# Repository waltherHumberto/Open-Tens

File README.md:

# Open-Tens
The goal of this project is to develop an open-source Transcutaneous Electrical Nerve Stimulation (TENS) system. TENS is a therapeutic technique that involves the application of low-voltage electrical currents to the skin, primarily for pain relief. This project aims to provide a platform for individuals and healthcare professionals to build and customize their own TENS devices using readily available hardware components.

The open-source nature of this project encourages collaboration, innovation, and the sharing of knowledge among developers and users. By making the TENS system accessible to a wider audience, we hope to empower individuals to explore alternative pain management techniques and contribute to the advancement of TENS technology.

Key Features and Objectives:

    Hardware Design: The project will provide detailed documentation and schematics for designing and building a TENS device. The emphasis will be on using affordable and easily obtainable components, making it accessible to hobbyists, researchers, and healthcare professionals.

    Software Development: The project will include software libraries and interfaces to control the TENS device. The software will allow users to adjust parameters such as frequency, pulse width, and intensity, providing a customizable and user-friendly experience.

    Safety and Effectiveness: Ensuring the safety and efficacy of the TENS system is of utmost importance. The project will focus on providing guidelines, best practices, and recommendations for safe usage, including electrical safety precautions and appropriate electrode placement.

    Community and Collaboration: The project aims to foster a supportive and collaborative community of developers, researchers, and users. This will be achieved through an online forum, issue tracking system, and regular updates to encourage discussions, bug reporting, feature requests, and contributions from the community.

By creating an open-source TENS system, we hope to democratize access to this pain management technique, encourage further research and development, and improve the lives of individuals suffering from chronic pain. Join us in this journey of innovation, empowerment, and open science.

Note: This project is not intended to replace professional medical advice or treatment. Users should consult with healthcare professionals before using the TENS system for any medical conditions or concerns.

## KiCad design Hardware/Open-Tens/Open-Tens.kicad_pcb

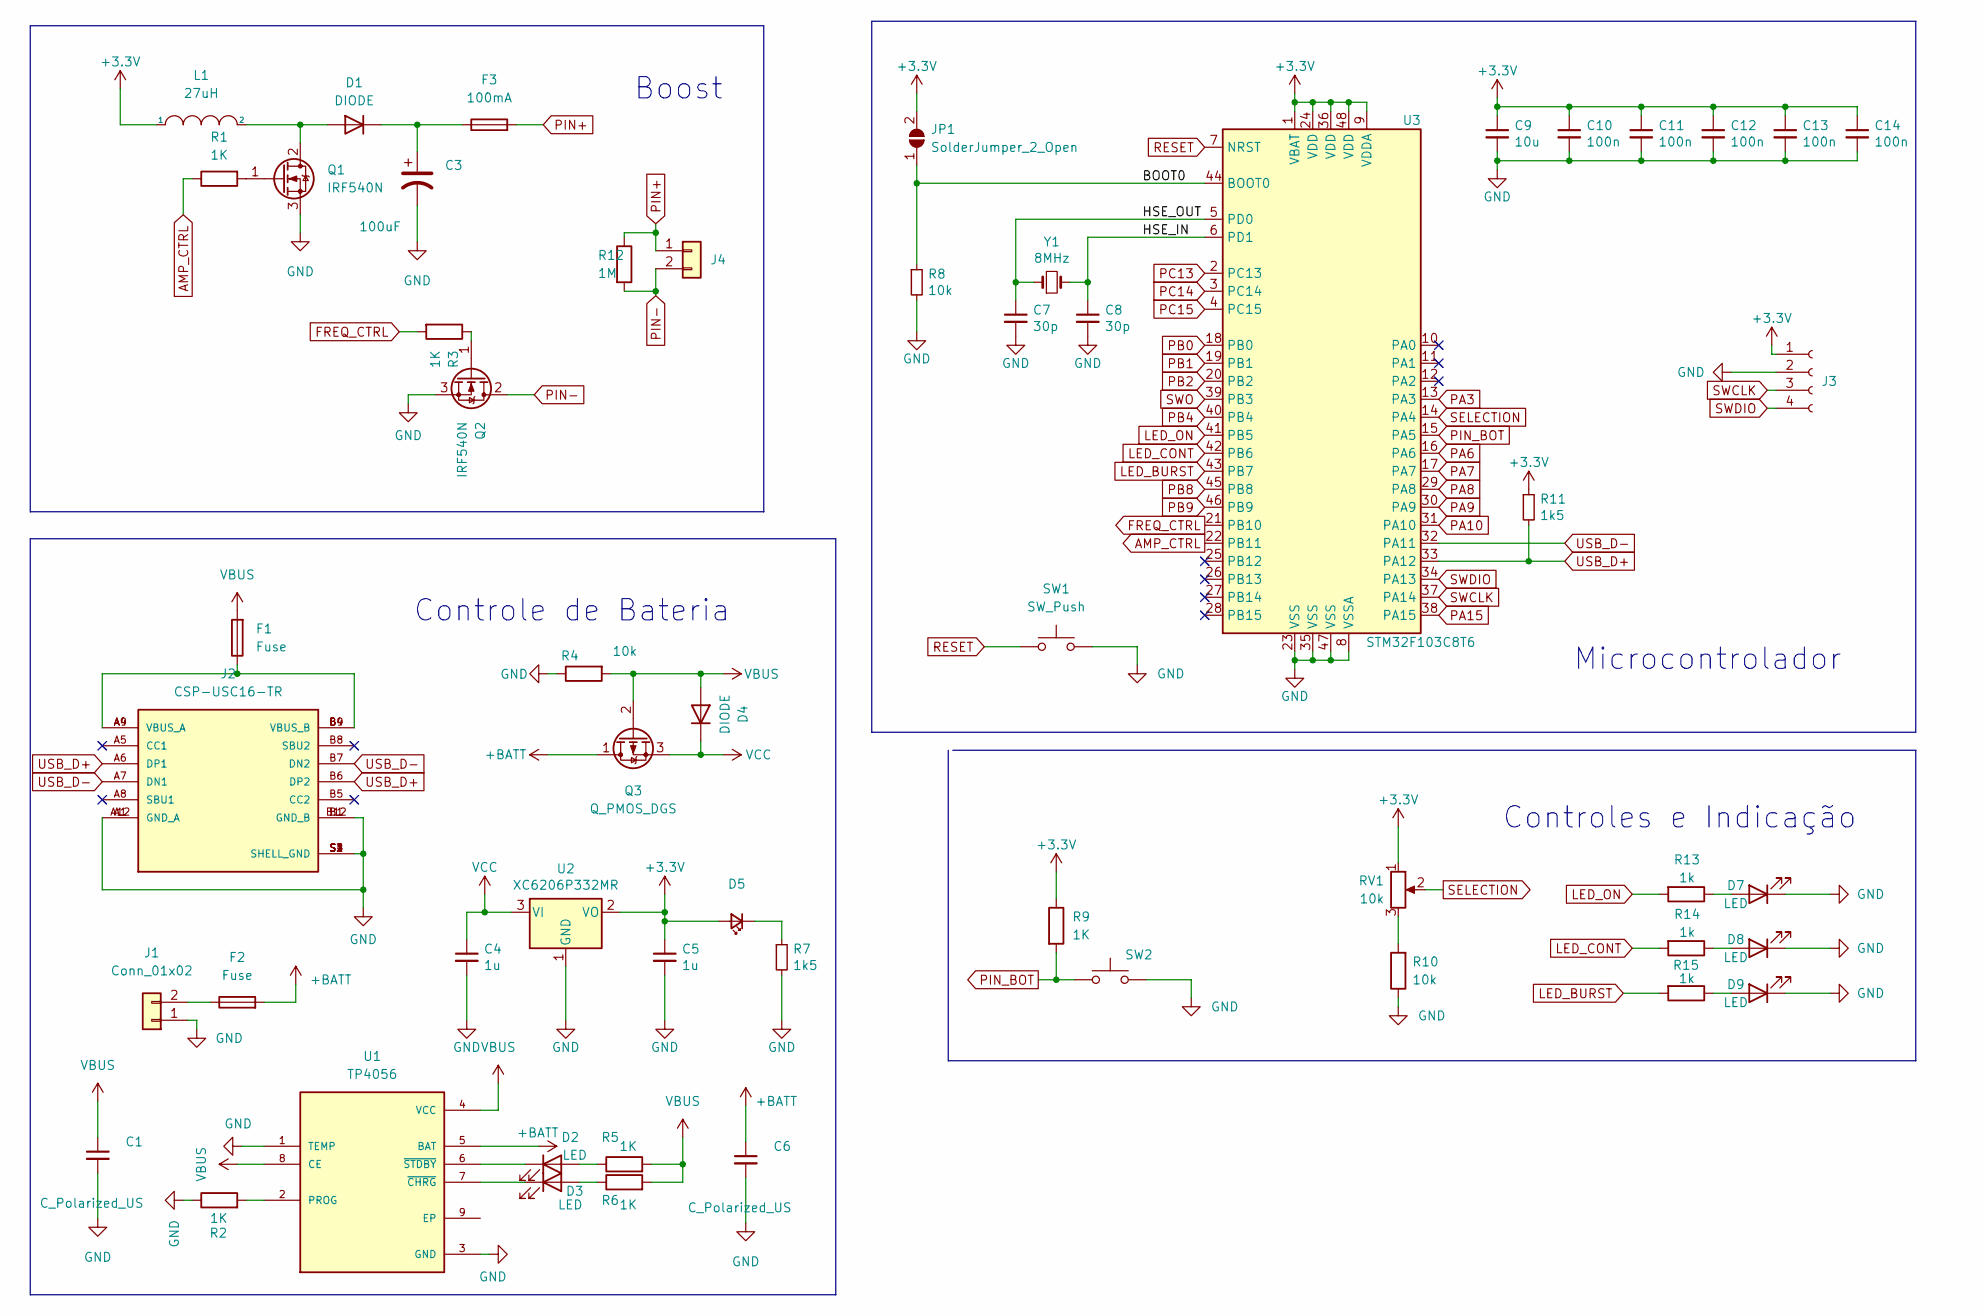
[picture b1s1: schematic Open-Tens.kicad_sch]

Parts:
C1, C6: C_Polarized_US; C_1210_3225Metric
C3: 100uF; CP_Radial_D10.0mm_P7.50mm
C4, C5: 1u; C_0603_1608Metric; LCSC Part # C15849
C7, C8: 30p; C_0402_1005Metric; LCSC Part # C1570
C9: 10u; C_1210_3225Metric; LCSC Part # C19666
C10, C11, C12, C13, C14: 100n; C_0402_1005Metric; LCSC Part # C1525
D1, D4: DIODE; D_1210_3225Metric
D2, D3, D7, D8, D9: LED; LED_D5.0mm_FlatTop
D5: LED; LED_D5.0mm_FlatTop; LCSC Part # C72043
F1, F2: Fuse; R_1206_3216Metric
F3: 100mA; R_1206_3216Metric
J1: Conn_01x02; PinSocket_1x02_P2.54mm_Vertical
J2: CSP-USC16-TR; USB_C_Receptacle_Palconn_UTC16-G; PARTREV A0
J3: Conn_01x04_Female; PinSocket_1x04_P2.54mm_Vertical
J4: Conn_01x02; R_Axial_DIN0309_L9.0mm_D3.2mm_P12.70mm_Horizontal
JP1: SolderJumper_2_Open; PinSocket_1x02_P2.54mm_Vertical
L1: 27uH; L_Taiyo-Yuden_NR-80xx_HandSoldering
Q1, Q2: IRF540N; TO-220-3_Vertical
Q3: Q_PMOS_DGS; SOT-23-3
R1, R2, R3, R5, R6, R9: 1K; R_0603_1608Metric
R4, R10: 10k; R_0603_1608Metric
R7: 1k5; R_0603_1608Metric; LCSC Part # C22843
R8: 10k; R_0603_1608Metric; LCSC Part # C25744
R11: 1k5; R_0603_1608Metric; LCSC Part # C25867
R12: 1M; R_Axial_DIN0309_L9.0mm_D3.2mm_P12.70mm_Horizontal
R13, R14, R15: 1k; R_0603_1608Metric
RV1: 10k; Potentiometer_Bourns_3296W_Vertical
SW1, SW2: SW_Push; SW_Push_1P1T_NO_CK_KSC6xxJ
U1: TP4056; SOP-8_3.9x4.9mm_P1.27mm
U2: XC6206P332MR; SOT-23; LCSC Part # C5446
U3: STM32F103C8T6; LQFP-48_7x7mm_P0.5mm; LCSC Part # C8734
Y1: 8MHz; Crystal_SMD_5032-2Pin_5.0x3.2mm; LCSC Part # C115962

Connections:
+3.3V: C5.1, C9.1, C10.1, C11.1, C12.1, C13.1, C14.1, D5.2 (A), J3.1, JP1.2 (B), L1.1, R9.1, R11.1, RV1.1, U2.2 (VO), U3.1 (VBAT), U3.9 (VDDA), U3.24 (VDD), U3.36 (VDD), U3.48 (VDD)
+BATT: C6.1, F2.2, Q3.1 (D), U1.5 (BAT)
/BOOT0: JP1.1 (A), R8.1, U3.44 (BOOT0)
/HSE_IN: C8.1, U3.6 (PD1), Y1.2
/HSE_OUT: C7.1, U3.5 (PD0), Y1.1
AMP_CTRL: R1.1, U3.22 (PB11)
FREQ_CTRL: R3.2, U3.21 (PB10)
GND: C1.2, C3.2, C4.2, C5.2, C6.2, C7.2, C8.2, C9.2, C10.2, C11.2, C12.2, C13.2, C14.2, D7.1 (K), D8.1 (K), D9.1 (K), J1.1, J2.A1 (GND_A), J2.A12 (GND_A), J2.B1 (GND_B), J2.B12 (GND_B), J2.S1 (SHELL_GND), J2.S2 (SHELL_GND), J2.S3 (SHELL_GND), J2.S4 (SHELL_GND), J3.2, Q1.3 (S), Q2.3 (S), R2.1, R4.1, R7.2, R8.2, R10.1, SW1.2, SW2.2, U1.1 (TEMP), U1.3 (GND), U2.1 (GND), U3.8 (VSSA), U3.23 (VSS), U3.35 (VSS), U3.47 (VSS); also elsewhere on the board
LED_BURST: R15.2, U3.43 (PB7)
LED_CONT: R14.2, U3.42 (PB6)
LED_ON: R13.2, U3.41 (PB5)
unnamed: C3.1, D1.2 (K), F3.1
unnamed: D1.1 (A), L1.2, Q1.2 (D)
unnamed: D2.1 (K), U1.6 (~STDBY)
unnamed: D2.2 (A), R5.1
unnamed: D3.1 (K), U1.7 (~CHRG)
unnamed: D3.2 (A), R6.1
unnamed: D5.1 (K), R7.1
unnamed: D7.2 (A), R13.1
unnamed: D8.2 (A), R14.1
unnamed: D9.2 (A), R15.1
unnamed: F1.1, J2.A4 (VBUS_A), J2.A9 (VBUS_A), J2.B4 (VBUS_B), J2.B9 (VBUS_B)
unnamed: F2.1, J1.2
unnamed: Q1.1 (G), R1.2
unnamed: Q2.1 (G), R3.1
unnamed: R2.2, U1.2 (PROG)
unnamed: R10.2, RV1.3
PA3: U3.13 (PA3)
PA6: U3.16 (PA6)
PA7: U3.17 (PA7)
PA8: U3.29 (PA8)
PA9: U3.30 (PA9)
PA10: U3.31 (PA10)
PA15: U3.38 (PA15)
PB0: U3.18 (PB0)
PB1: U3.19 (PB1)
PB2: U3.20 (PB2)
PB4: U3.40 (PB4)
PB8: U3.45 (PB8)
PB9: U3.46 (PB9)
PC13: U3.2 (PC13)
PC14: U3.3 (PC14)
PC15: U3.4 (PC15)
PIN+: F3.2, J4.1, R12.1
PIN-: J4.2, Q2.2 (D), R12.2
PIN_BOT: R9.2, SW2.1, U3.15 (PA5); also elsewhere on the board
RESET: SW1.1, U3.7 (NRST); also elsewhere on the board
SELECTION: RV1.2, U3.14 (PA4)
SWCLK: J3.3, U3.37 (PA14)
SWDIO: J3.4, U3.34 (PA13)
SWO: U3.39 (PB3)
USB_D+: J2.A6 (DP1), J2.B6 (DP2), R11.2, U3.33 (PA12)
USB_D-: J2.A7 (DN1), J2.B7 (DN2), U3.32 (PA11)
VBUS: C1.1, D4.1 (A), F1.2, Q3.2 (G), R4.2, R5.2, R6.2, U1.4 (VCC), U1.8 (CE)
VCC: C4.1, D4.2 (K), Q3.3 (S), U2.3 (VI)

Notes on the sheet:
Controle de Bateria
Controles e Indicação
Boost
Microcontrolador

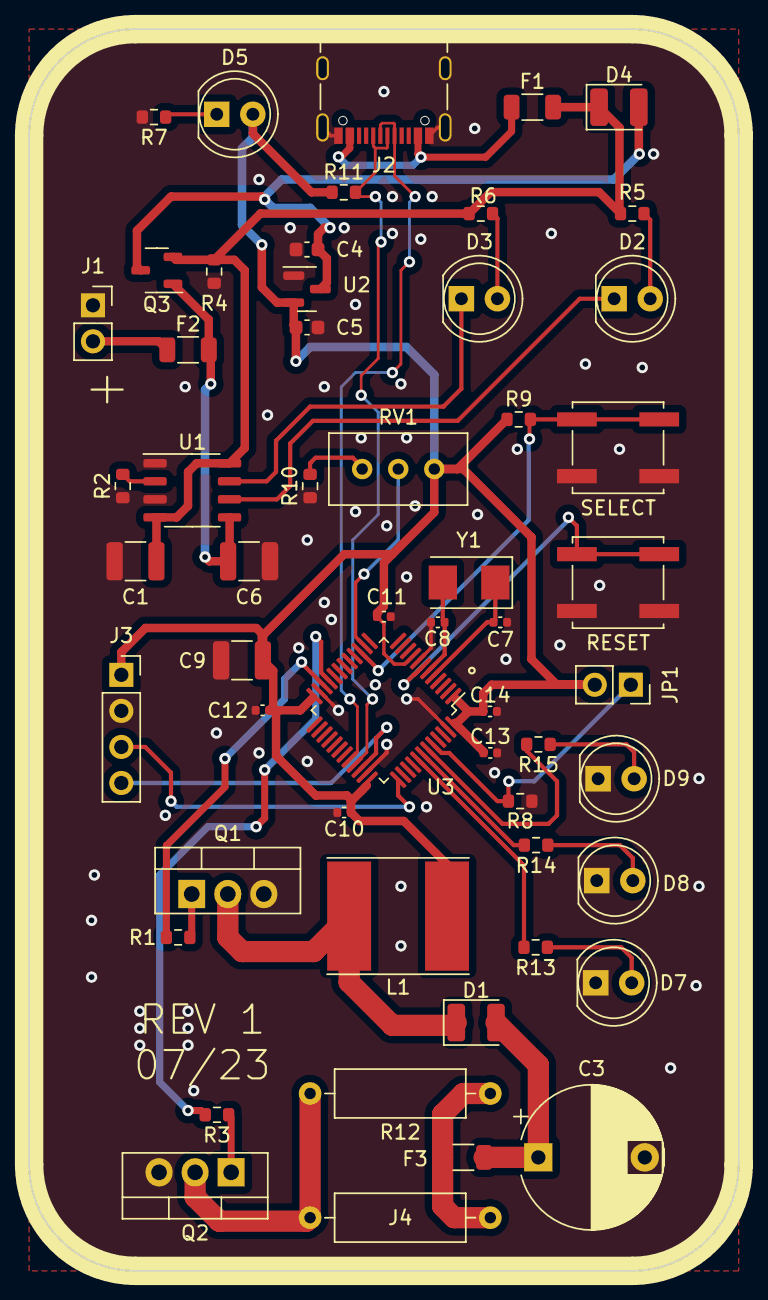
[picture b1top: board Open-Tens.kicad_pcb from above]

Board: 2 copper layers, 50.0 x 87.5 mm, 55 parts (0 on the bottom side), 38 nets.

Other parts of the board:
RESET: SW_Push; SW_Push_1P1T_NO_CK_KSC6xxJ
SELECT: SW_Push; SW_Push_1P1T_NO_CK_KSC6xxJ

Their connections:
GND: RESET.2, SELECT.2; also elsewhere on the board
PIN_BOT: SELECT.1; also elsewhere on the board
RESET: RESET.1; also elsewhere on the board

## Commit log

2023-07-06 Update README.md
    Adding context to README
2023-07-09 Saving to push
2023-07-11 Separando o esquematico falta colocar valores
2023-07-13 Trocando o micro para stm32
2023-07-13 Comecei a colocar alguns footprints
2023-07-14 Fiz um roteamento completo mas vou revisar e refazer
